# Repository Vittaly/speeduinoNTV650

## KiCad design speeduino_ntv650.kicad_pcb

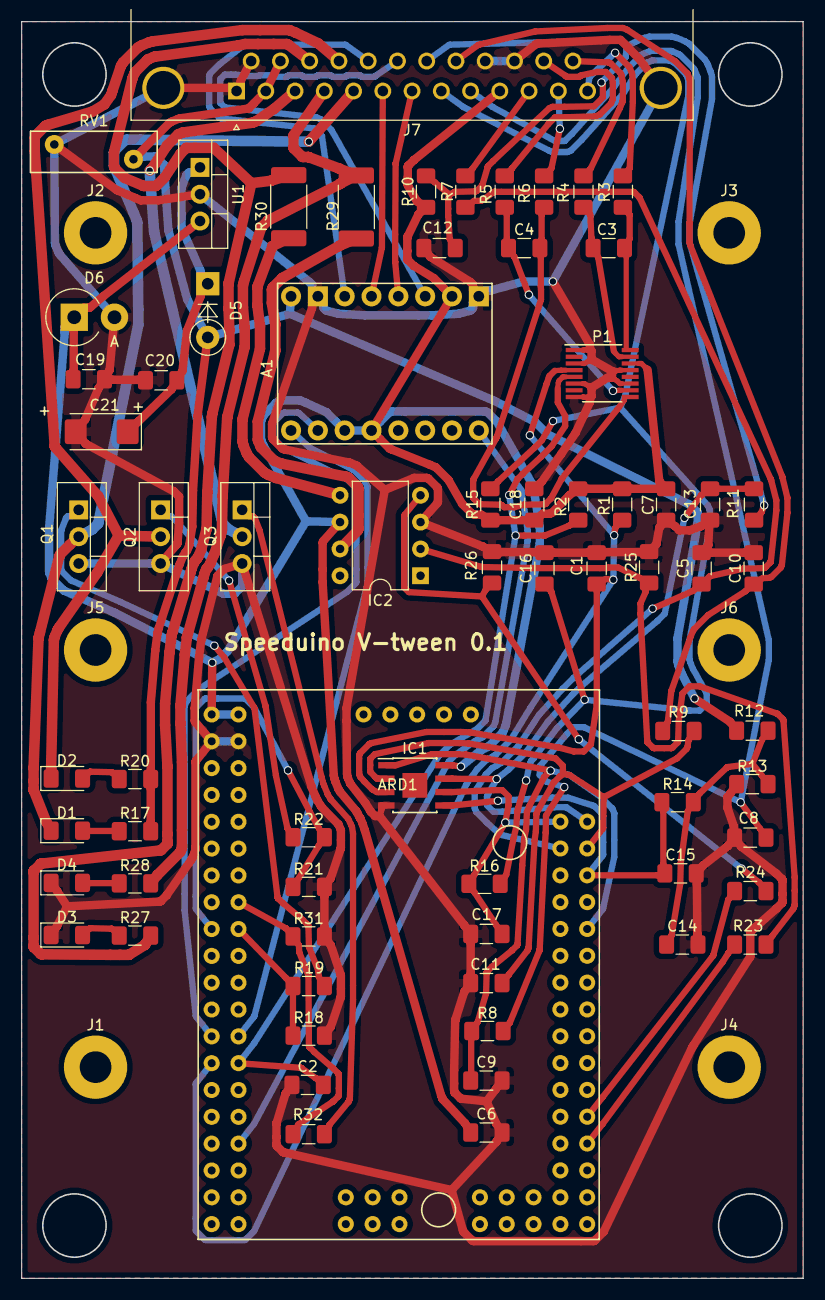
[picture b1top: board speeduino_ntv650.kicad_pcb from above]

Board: 2 copper layers, 74.0 x 119.0 mm, 76 parts (0 on the bottom side), 54 nets.

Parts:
A1: Pololu_Breakout_A4988; A4988 Stepper Motor Driver Carrier
ARD1: ArduinoMegaProMini
C1: 0.01mF; C_1206_3216Metric_Pad1.42x1.75mm_HandSolder
C2: 0.22mF; C_1206_3216Metric_Pad1.42x1.75mm_HandSolder
C3, C4: 1nF; C_1206_3216Metric_Pad1.42x1.75mm_HandSolder
C5: 0.3uF; C_1206_3216Metric_Pad1.42x1.75mm_HandSolder
C6, C18: 1uF; C_1206_3216Metric_Pad1.42x1.75mm_HandSolder
C7: 0.01uF; C_1206_3216Metric_Pad1.42x1.75mm_HandSolder
C8, C10, C12, C14, C16, C20: 0.1uF; C_1206_3216Metric_Pad1.42x1.75mm_HandSolder
C9, C11, C13, C15, C17: 0.22uF; C_1206_3216Metric_Pad1.42x1.75mm_HandSolder
C19: 10uF; CP_EIA-6032-15_Kemet-U
C21: 47uF; C_1206_3216Metric_Pad1.42x1.75mm_HandSolder
D1, D2: LED INJ; LED_1206_3216Metric_Pad1.42x1.75mm_HandSolder
D3: LED AGN2; LED_1206_3216Metric_Pad1.42x1.75mm_HandSolder
D4: LED AGN1; LED_1206_3216Metric_Pad1.42x1.75mm_HandSolder
D5: 1N5818; D_DO-41_SOD81_P5.08mm_Vertical_KathodeUp
D6: 1N5919BG; D_DO-201_P3.81mm_Vertical_AnodeUp
IC1: SP721; SOIC-8-1EP_3.9x4.9mm_Pitch1.27mm
IC2: TC4424; DIP-8_W7.62mm
J1, J2, J3, J4, J5, J6: Conn_01x01; MountingHole_3mm_Pad
J7: DB25_Female_MountingHoles; DSUB-25_Female_Horizontal_P2.77x2.84mm_EdgePinOffset4.94mm_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
P1: MAX9926_9927; QSOP-16_3.9x4.9mm_Pitch0.635mm
Q1, Q2, Q3: STP62NS04Z; TO-220-3_Vertical
R1, R2: 1k; R_1206_3216Metric_Pad1.42x1.75mm_HandSolder
R3, R4, R5, R6: 10k; R_1206_3216Metric_Pad1.42x1.75mm_HandSolder
R7: 750; R_1206_3216Metric_Pad1.42x1.75mm_HandSolder
R8, R9, R11, R14, R16: 470; R_1206_3216Metric_Pad1.42x1.75mm_HandSolder
R10, R15: 2.49K; R_1206_3216Metric_Pad1.42x1.75mm_HandSolder
R12: 3.9K; R_1206_3216Metric_Pad1.42x1.75mm_HandSolder
R13, R19, R22, R23, R24, R32: 1K; R_1206_3216Metric_Pad1.42x1.75mm_HandSolder
R17, R20, R27, R28: 2.4K; R_1206_3216Metric_Pad1.42x1.75mm_HandSolder
R18, R21, R25, R26, R31: 100K; R_1206_3216Metric_Pad1.42x1.75mm_HandSolder
R29, R30: 160; R_2512_6332Metric_Pad1.52x3.35mm_HandSolder
RV1: ERZV14D220; RV_Disc_D12_W3.9_P7.5
U1: LM2937xT; TO-220-3_Vertical

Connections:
5V: A1.2, A1.13, A1.14, ARD1.81, ARD1.88, C6.1, C7.1, C18.1, C21.1, D6.1, IC1.8, IC2.6, J7.10, P1.14, R1.1, R2.1, R10.1, R15.1, U1.3
12V: A1.8, D5.2, J7.2, J7.15, R12.2, R17.2, R20.2, RV1.1
+12V: C19.1, C20.1, D5.1, U1.1
ADC-Clamp1: ARD1.62, C9.1, IC1.1, R8.1
ADC-Clamp2: ARD1.55, C17.1, IC1.6, R16.1
ADC-Clamp3: ARD1.56, C11.1, IC1.2, R9.1
ADC-Clamp4: ARD1.58, C15.1, IC1.5, R14.1
ADC-Clamp5: ARD1.19, C1.2, IC1.3, P1.4, R1.2
ADC-Clamp6: ARD1.54, C13.1, IC1.7, R11.1
CLT_sens: C16.1, J7.8, R15.2, R16.2
GND: A1.1, A1.7, ARD1.80, ARD1.87, C1.1, C2.1, C5.2, C6.2, C7.2, C8.2, C9.2, C10.2, C11.2, C12.2, C13.2, C14.2, C15.2, C16.2, C17.2, C18.2, C19.2, C20.2, C21.2, D3.1, D4.1, D6.2, IC1.4, IC2.3, J7.0, J7.1, J7.14, J7.22, J7.23, P1.1, P1.3, P1.6, P1.8, P1.11, P1.13, Q1.3, Q2.3, Q3.3, R13.1, R18.2, R21.2, R25.2, R26.1, R31.2, RV1.2, U1.2
IDLE-CPU-D6: ARD1.6, R31.1, R32.2
IGN1-CPU-D40: ARD1.40, R23.2
IGN2-CPU-D38: ARD1.38, R24.2
INJ1-CPU-D8: ARD1.8, R18.1, R19.2
INJ2-CPU-D9: ARD1.9, R21.1, R22.2
ITS_sens: C12.1, J7.20, R10.2, R11.2
MAP: J7.11, R7.2
MAP-CPU-A3: ARD1.57, C5.1, R7.1
unnamed: C3.1, P1.16, R3.2
unnamed: C3.2, P1.15, R4.2
unnamed: C4.1, P1.10, R5.2
unnamed: C4.2, P1.9, R6.2
unnamed: C14.1, R12.1, R13.2, R14.2
unnamed: D1.2, R17.1
unnamed: D2.2, R20.1
unnamed: D3.2, R27.1
unnamed: D4.2, R28.1
unnamed: IC2.2, R23.1, R25.1
unnamed: IC2.4, R24.1, R26.2
unnamed: IC2.5, R30.2
unnamed: IC2.7, R29.2
unnamed: Q1.1, R19.1
unnamed: Q2.1, R22.1
unnamed: Q3.1, R32.1
O2_sens: C8.1, J7.9, R8.2
STEP-1A-OUT: A1.4, J7.7
STEP-1B-OUT: A1.3, J7.19
STEP-2A-OUT: A1.5, J7.6
STEP-2B-OUT: A1.6, J7.18
STEP-CPU-D17: A1.15, ARD1.17
STEPDIR-CPU-D16: A1.16, ARD1.16
STEPEN-CPU-D24: A1.9, ARD1.24
TACH2-CPU-D18: ARD1.18, C2.2, P1.5, R2.2
TPS_sens: C10.1, J7.21, R9.2
VR1+: J7.13, R3.1
VR1-: J7.25, R4.1
VR2+: J7.12, R6.1
VR2-: J7.24, R5.1
idle-out: J7.3, Q3.2
ign-1-out: J7.4, R28.2, R29.1
ign-2-out: J7.16, R27.2, R30.1
inj-1-out: D1.1, J7.5, Q1.2
inj-2-out: D2.1, J7.17, Q2.2

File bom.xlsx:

| Sourced | Placed | References | Value | Footprint | Quantity
1 |  |  | C7, C9, C11, C13, C15, C19 | 0.1uF | C_Axial_L5.1mm_D3.1mm_P7.50mm_Horizontal | 6
2 |  |  | C8, C10, C12, C14, C16 | 0.22uF | C_Axial_L5.1mm_D3.1mm_P7.50mm_Horizontal | 5
3 |  |  | C1, C18 | 10uF | C_Axial_L5.1mm_D3.1mm_P7.50mm_Horizontal | 2
4 |  |  | C2, C3 | 1nF | C_Axial_L5.1mm_D3.1mm_P7.50mm_Horizontal | 2
5 |  |  | C5, C17 | 1uF | C_Axial_L5.1mm_D3.1mm_P7.50mm_Horizontal | 2
6 |  |  | C4 | 0.3uF | C_Axial_L5.1mm_D3.1mm_P7.50mm_Horizontal | 1
7 |  |  | C6 | 0.01uF | C_Axial_L5.1mm_D3.1mm_P7.50mm_Horizontal | 1
8 |  |  | R1, R2, R13, R19, R22, R23, R24, R32 | 1K | R_2010_5025Metric | 8
9 |  |  | R8, R9, R11, R14, R16 | 470 | R_2010_5025Metric | 5
10 |  |  | R18, R21, R25, R26, R31 | 100K | R_2010_5025Metric | 5
11 |  |  | R3, R4, R5, R6 | 10k | R_2010_5025Metric | 4
12 |  |  | R17, R20, R27, R28 | 2.4K | R_2010_5025Metric | 4
13 |  |  | R10, R15 | 2.49K | R_2010_5025Metric | 2
14 |  |  | R29, R30 | 160 | R_2010_5025Metric | 2
15 |  |  | R7 | 750 | R_2010_5025Metric | 1
16 |  |  | R12 | 3.9K | R_2010_5025Metric | 1
17 |  |  | D2, D4 | D | D_DO-41_SOD81_P7.62mm_Horizontal | 2
18 |  |  | D7 | 1N5818 | D_DO-41_SOD81_P7.62mm_Horizontal | 1
19 |  |  | D8 | 1N5919BG | D_DO-41_SOD81_P7.62mm_Horizontal | 1
20 |  | ✓ | D1, D3 | LED INJ | LED_D5.0mm | 2
21 |  | ✓ | D5 | LED AGN2 | LED_D5.0mm | 1
22 |  | ✓ | D6 | LED AGN1 | LED_D5.0mm | 1
23 |  |  | U1 | LM2937xT | TO-220-3_Vertical | 1
24 | ✓ |  | A1 | Pololu_Breakout_A4988 | A4988 Stepper Motor Driver Carrier | 1
25 | ✓ |  | ARD1 | ArduinoMegaProMini | ArduinoMegaProMini | 1
26 |  |  | RV1 | ERZV14D220 | RV_Disc_D12_W3.9_P7.5 | 1
27 |  |  | IC1 | SP721 | SOIC-8-1EP_3.9x4.9mm_Pitch1.27mm | 1
28 | ✓ |  | IC2 | TC4424 | SOIC-8_3.9x4.9mm_Pitch1.27mm | 1
29 | ✓ |  | Q1, Q2, Q3 | STP62NS04Z | TO-220-3_Vertical | 3
30 |  |  | J1 | Conn_01x25_DB-25 | DSUB-25_Male_Horizontal_P2.77x2.84mm_EdgePinOffset9.90mm_Housed_MountingHolesOf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 | 1
31 | ✓ |  | P1 | MAX9926_9927 | QSOP-16_3.9x4.9mm_Pitch0.635mm | 1

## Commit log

2019-08-22 'first'
2019-08-22 second commit
2019-08-22 add file for map
2019-08-23 path to project library was fixed
2019-08-23 added gitignore, added connector
2019-08-24 added sens
2019-08-24 added ign
2019-08-24 fixed some errors
2019-08-24 added new blocks
2019-08-25 some footprint was seted
2019-08-26 add footprints
2019-08-29 first routing
2019-08-29 add net classes
2019-08-29 changed connector points
2019-08-29 second routs
2019-08-29 freeRoute result
2019-08-30 attempt
2019-08-30 change footprints
2019-08-30 added bom
2019-09-01 first complited pcb
2019-09-04 new routes
2019-09-09 pcb size chaged
2019-09-11 changed footprints
2019-09-12 rv line joined
2019-09-12 routing
2019-09-16 fixed errors
2019-09-23 changed its sens schema
2019-10-07 pcb frame complited
2019-10-08 pcb change some positions
2019-10-08 pcb change some positions again
2019-10-09 routing complite
2019-10-10 new element positions for 0.6 mm lines on pcb
2019-10-11 new routing
2019-10-11 remove mounting holes from gnd net
2019-10-13 routing with fat traks
2019-10-28 move via from under max ic
2019-11-11 rm clump
2019-11-11 new component
2019-11-14 routing with topor
2019-11-15 add arduino docs
2019-11-27 gerbers
2019-11-27 last changes
2019-12-21 reroute again
2020-01-03 rm diores from led circuits, change to 1206
2020-01-03 new gerber
